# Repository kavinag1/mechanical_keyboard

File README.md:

# Building My Own 60% Mechanical Keyboard with a Raspberry Pi Pico

I have been wanting a mechanical keyboard. So instead of buying one why not make one. This was not really a easy journey but I am proud of what all I have learnt

---

## The Journey

### Step 0: Deciding the keyboard (1hr)
Over the past few days, I researched different types of keyboards to decide what I want to build. I compared layouts like 40%, 60%, 65%, and TKL, and chose a 60% layout because it offers a good balance between size and functionality while still being manageable to design. I also looked at existing open-source designs like the CO60 to understand how keyboard PCBs are structured and to confirm standard design practices.

I also researched switches, connectivity, and firmware. I selected EPOMAKER Creamy Jade switches because they are MX-style and compatible with standard footprints. I decided to make the keyboard wired instead of wireless to reduce complexity and allow me to use QMK firmware more easily.

The final specifications of my keyboard include a 60% layout, MX-style 5-pin switches, a row-column matrix with 1N4148 diodes, USB-C connectivity, and an STM32-based microcontroller. I will also include a rotary encoder for extra functionality and simple per-key backlighting. This research helped me clearly define my design before moving on to the PCB stage.

### Step 1: Learning What a Keyboard Matrix Is (1.5hr)

so before I could build this keyboard I needed to pratice what keyboard matrix is and understand how it works. So I followed a tutorial to make a simple and easy 3 by 3 keybaord matrix like the one you can see in the image. Keyboard matrix allows you to add more keys and use less number of pins like here I used 9 keys but only used 6 pins. This would be useful in the future when making the actual keyboard cause raspberry pico has only so many number of pins.

Once I understood the concept, I mapped out the full 60-key layout I wanted to build — a standard 60% ANSI arrangement: 5 rows and 14 columns.
this is the layout of the keyboard I went with

---

### Step 2: Designing the Schematic (2hr)

now after finalising the layout of my keyboard I needed to make the schematic of the keyboard. each key would need a switch and then a diode connected to it to prevnt phantom keypresses as if the diode are not present, when you are pressing multiple keys some keys you didnt press will also register and we dont want that. So I arranged the keys in a form of a matrix then conected the rows and collom pins to my GPIO pin in the pico. and then I also added a oled screen and a knob for the keyabord cause why not.

---

### Step 3: Routing the PCB (1hr)

With the schematic done, I moved on to laying out and routing the actual PCB. 

the peices I used are given in the BOM if you want to use the same parts

---

### Step 4:Writing the firmware (1.3hr)

The firmware was developed to act as the core software controlling the mechanical keyboard. I configured the keyboard's key matrix so that every physical switch was correctly mapped to its corresponding keycode and created a custom keymap defining the functionality of each key. 

### Step 5: adding the screen and the knob (3hr)

later on I wanted to add the knob and scren as well. for which I had to change the entire PCB again as I need to create more space for both of them. It took me some time to get the pcb right again. So I had to reroute all the wires makwe the scehmatic again and finally I was able to make it. I also had to make changes to the firmware code.

### Step 6: Designing the Case (2hr + 2hr)

I designed the case two times first was without the screen and the knob and was very basic because I spent time figuuring out how to add the spaces for the keyboard in the first design and then later I changed it to a more ergonomic design.

Then the final step was designing the case itself. For this I would reccomened exporting the PCB as a stl file and adding it in your cad to see if it fits your case or not. It saved me multiple times as I messed up the dimensions but this is the final case I eneded up with which perectly fits the PCB inside. for the case as you can see I went with a open desgin wherethe top part is open so that i can somewhat see the PCB just to remind me this is something I have created on my own.

### Step 7: making the case cooler (2hr)

after desiging the case I though of adding something on the back. For that I decided an engraving of the character brook from one peice./ So for that first i found and took inpiration from an arrt to create one fro the aspoect ratio of my keyboard. After which I uploaded the art on inkscape where i made the bitmap of the art. then i saved it as a dxf file which then I imported on onshape. AFter importing I resized itg and placed it on my case. I tried to extrude the whole sketch as it is but that didnt work because some part of the sketch broke. So I slowly divided it into difffernt parts and did it one by one. Overall I am pretty happy with the design.

## Bill of Materials

| Component | Purpose | Qty | Cost (USD) | Distributor | Link |
|-----------|---------|-----|-----------|-------------|------|
| Screen | The screen for the keyboard | 1 | $1.56 | Tech Delivers | [Buy](https://techdelivers.com/0-91-inch-oled-lcd-display-module-blue-128x32-i2c-iic-serial?tag=i2c%20lcd) |
| Micro USB Cable | To connect the Pico | 1 | $0.41 | robo craze | [Buy](https://robocraze.com/products/usb-to-micro-usb-cable?variant=40192442007705&country=IN&currency=INR&utm_medium=product_sync&utm_source=google&utm_content=sag_organic&utm_campaign=sag_organic&srsltid=AfmBOortLt6ed0G2jRT6m1UXHGk12v08zHm9dfpipg29VpxJJs0qQCNhlS8) |
| M2 Heat Set Inserts | For case assembly | 1 pack | $0.46 | Robu | [Buy]([https://www.amazon.in/BRASS-WAREHOUSE-Knurled-Threaded-Printing/dp/B0FMPZ3QHL/](https://robu.in/product/m2-x-4-mm-brass-insert/?gad_source=1&gad_campaignid=20387462343&gclid=CjwKCAjwqazPBhALEiwAOuXqdC2PIeLO9FYv27_n0XlEfAAc_tk7Q5QmU1Lylw90cpicqalJPc0k0xoC1_0QAvD_BwE&gbraid=0AAAAADvLFWezTS72c1S_AY11boPv9muTl)) |
| M2 Screws (20 pack) | Screwing the case | 1 pack | $1.5 | Robu | [Buy]([https://www.amazon.in/Tia-Golden-Screws-Length-Approx-480pcs/dp/B07VWKBHYZ/](https://robu.in/product/easymech-ss-304-csk-countersunk-philips-head-m2-x-8-mm-bolt-25-pcs/?gbraid=0AAAAADvLFWezTS72c1S_AY11boPv9muTl&gclid=CjwKCAjwqazPBhALEiwAOuXqdAjEcDjzmP8nFjrnLJZwyW1j_63GiNewVw8KRRNHgBSEja_1QjdDzRoC5vAQAvD_BwE&gad_source=1&gad_campaignid=20387462343) |
| Keycaps | Keycaps for the keyboard | 1 set | $13.5 | curisosity caps | [Buy]([https://meckeys.com/shop/accessories/keyboard-accessories/keycaps/grey-black-keycaps/](https://curiositycaps.in/products/cloud-lake-cherry-doubleshot-pbt-keycaps?_pos=14&_fid=805e1adb4&_ss=c)) |
| Gateron Switches | Switches for the keys | 7 packs | $13.37 | stackskb | [Buy]([https://meckeys.com/shop/accessories/keyboard-accessories/key-switches/gateron-optical-switch-pack/](https://stackskb.com/store/click-inc-of-linear-switch-pack-of-10/)) |
| Raspberry Pi Pico | The brain | 1 | $4.00 | Robu.in | [Buy](https://robu.in/product/raspberry-pi-pico/) |
| 3D Printed Case | The case | 1 | $16.18 | Robo In | — |
| DIODE | Its the diode for the circuit | 100 | $1.02 | Robu | [Buy]([https://www.amazon.in/Circuit-Ranger-Switching-Electronic-Projects/dp/B0FJLP12GX](https://robu.in/product/1n4148-1w-zener-diode-pack-of-50/?gclid=CjwKCAjwqazPBhALEiwAOuXqdDxSeVSHAfyNggbR2lhy_VAFvBNVaP29-qa4l7G2ySUgKkgBtbLfTRoC0zQQAvD_BwE&gad_campaignid=17427802703&gbraid=0AAAAADvLFWfPaMOUeeB-SFTwcKxeFjDbO&gad_source=1)) |
| PCB | It is the pcb of the keyboard | 5 | $64 | JLCPCB | — |
| **Total** | | | **$116** | | |

---

rols.

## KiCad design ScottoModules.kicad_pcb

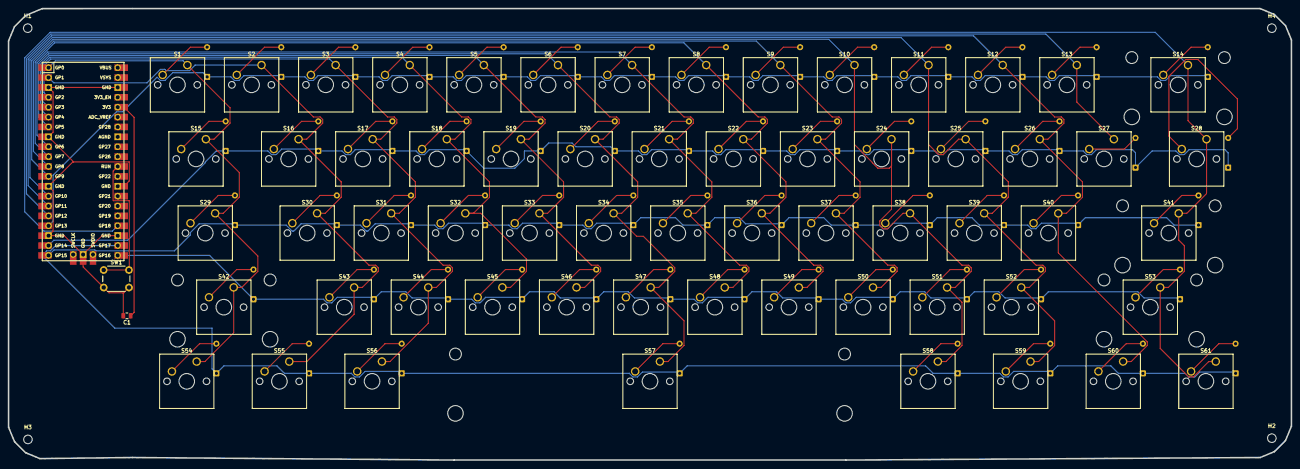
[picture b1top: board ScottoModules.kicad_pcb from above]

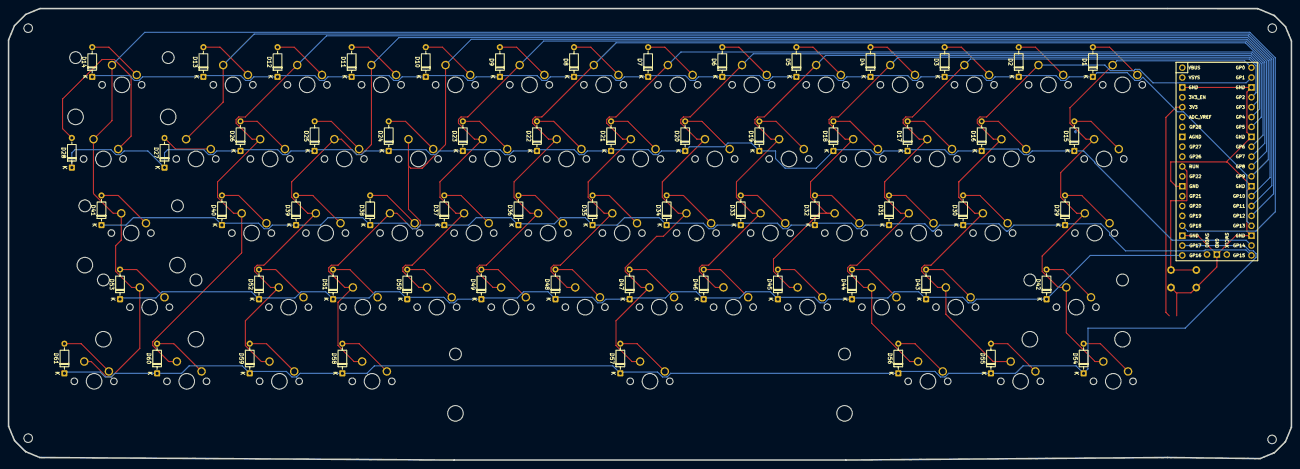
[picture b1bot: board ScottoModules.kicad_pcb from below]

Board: 4 copper layers, 329.7 x 116.0 mm, 129 parts (61 on the bottom side), 83 nets.

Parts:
C1: 0.1uF; C_0805_2012Metric
D1, D2, D3, D4, D5, D6, D7, D8, D9, D10, D11, D12, D13, D14, D15, D16, D17, D18, D19, D20, D21, D22, D23, D24, D25, D26, D27, D28, D29, D30, D31, D32, D33, D34, D35, D36, D37, D38, D39, D40, D41, D42, D43, D44, D45, D46, D47, D48, D49, D50, D51, D52, D53, D54, D55, D56, D57, D58, D59, D60, D61: D_DO-35_SOD27_P7.62mm_Horizontal
H1, H2, H3, H4: MountingHole; MountingHole_2.2mm_M2
S1, S2, S3, S4, S5, S6, S7, S8, S9, S10, S11, S12, S13, S16, S17, S18, S19, S20, S21, S22, S23, S24, S25, S26, S27, S30, S31, S32, S33, S34, S35, S36, S37, S38, S39, S40, S43, S44, S45, S46, S47, S48, S49, S50, S51, S52: SW_Cherry_MX_1.00u_PCB
S14: SW_Cherry_MX_2.00u_PCB
S15, S28: SW_Cherry_MX_1.50u_PCB
S29: SW_Cherry_MX_1.75u_PCB
S41, S42: SW_Cherry_MX_2.25u_PCB
S53: SW_Cherry_MX_2.75u_PCB
S54, S55, S56, S58, S59, S60, S61: SW_Cherry_MX_1.25u_PCB
S57: SW_Cherry_MX_6.25u_PCB
SW1: SW_Push; SW_PUSH_6mm
U2: Raspberry_Pi_Pico

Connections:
GND: C1.2, SW1.2, U2.3 (GND), U2.8 (GND), U2.13 (GND), U2.18 (GND), U2.23 (GND), U2.28 (GND), U2.38 (GND), U2.42 (GND)
unnamed: D1.2 (A), S1.2
unnamed: D2.2 (A), S2.2
unnamed: D3.2 (A), S3.2
unnamed: D4.2 (A), S4.2
unnamed: D5.2 (A), S5.2
unnamed: D6.2 (A), S6.2
unnamed: D7.2 (A), S7.2
unnamed: D8.2 (A), S8.2
unnamed: D9.2 (A), S9.2
unnamed: D10.2 (A), S10.2
unnamed: D11.2 (A), S11.2
unnamed: D12.2 (A), S12.2
unnamed: D13.2 (A), S13.2
unnamed: D14.2 (A), S14.2
unnamed: D15.2 (A), S15.2
unnamed: D16.2 (A), S16.2
unnamed: D17.2 (A), S17.2
unnamed: D18.2 (A), S18.2
unnamed: D19.2 (A), S19.2
unnamed: D20.2 (A), S20.2
unnamed: D21.2 (A), S21.2
unnamed: D22.2 (A), S22.2
unnamed: D23.2 (A), S23.2
unnamed: D24.2 (A), S24.2
unnamed: D25.2 (A), S25.2
unnamed: D26.2 (A), S26.2
unnamed: D27.2 (A), S27.2
unnamed: D28.2 (A), S28.2
unnamed: D29.2 (A), S29.2
unnamed: D30.2 (A), S30.2
unnamed: D31.2 (A), S31.2
unnamed: D32.2 (A), S32.2
unnamed: D33.2 (A), S33.2
unnamed: D34.2 (A), S34.2
unnamed: D35.2 (A), S35.2
unnamed: D36.2 (A), S36.2
unnamed: D37.2 (A), S37.2
unnamed: D38.2 (A), S38.2
unnamed: D39.2 (A), S39.2
unnamed: D40.2 (A), S40.2
unnamed: D41.2 (A), S41.2
unnamed: D42.2 (A), S42.2
unnamed: D43.2 (A), S43.2
unnamed: D44.2 (A), S44.2
unnamed: D45.2 (A), S45.2
unnamed: D46.2 (A), S46.2
unnamed: D47.2 (A), S47.2
unnamed: D48.2 (A), S48.2
unnamed: D49.2 (A), S49.2
unnamed: D50.2 (A), S50.2
unnamed: D51.2 (A), S51.2
unnamed: D52.2 (A), S52.2
unnamed: D53.2 (A), S53.2
unnamed: D54.2 (A), S54.2
unnamed: D55.2 (A), S55.2
unnamed: D56.2 (A), S56.2
unnamed: D57.2 (A), S57.2
unnamed: D58.2 (A), S58.2
unnamed: D59.2 (A), S59.2
unnamed: D60.2 (A), S60.2
unnamed: D61.2 (A), S61.2
unnamed: C1.1, U2.36 (3V3)
column 0: S1.1, S15.1, S29.1, S42.1, S54.1, U2.1 (GPIO0)
column 1: S2.1, S16.1, S30.1, S43.1, S55.1, U2.2 (GPIO1)
column 2: S3.1, S17.1, S31.1, S44.1, S56.1, U2.4 (GPIO2)
column 3: S4.1, S18.1, S32.1, S45.1, U2.5 (GPIO3)
column 4: S5.1, S19.1, S33.1, S46.1, U2.6 (GPIO4)
column 5: S6.1, S20.1, S34.1, S47.1, S57.1, U2.7 (GPIO5)
column 6: S7.1, S21.1, S35.1, S48.1, U2.9 (GPIO6)
column 7: S8.1, S22.1, S36.1, S49.1, U2.10 (GPIO7)
column 8: S9.1, S23.1, S37.1, S50.1, U2.11 (GPIO8)
column 9: S10.1, S24.1, S38.1, S51.1, S58.1, U2.12 (GPIO9)
column 10: S11.1, S25.1, S39.1, S52.1, S59.1, U2.14 (GPIO10)
column 11: S12.1, S26.1, S40.1, S60.1, U2.15 (GPIO11)
column 12: S13.1, S27.1, U2.16 (GPIO12)
column 13: S14.1, S28.1, S41.1, S53.1, S61.1, U2.24 (GPIO18)
row 0: D1.1 (K), D2.1 (K), D3.1 (K), D4.1 (K), D5.1 (K), D6.1 (K), D7.1 (K), D8.1 (K), D9.1 (K), D10.1 (K), D11.1 (K), D12.1 (K), D13.1 (K), D14.1 (K), U2.17 (GPIO13)
row 1: D15.1 (K), D16.1 (K), D17.1 (K), D18.1 (K), D19.1 (K), D20.1 (K), D21.1 (K), D22.1 (K), D23.1 (K), D24.1 (K), D25.1 (K), D26.1 (K), D27.1 (K), D28.1 (K), U2.19 (GPIO14)
row 2: D29.1 (K), D30.1 (K), D31.1 (K), D32.1 (K), D33.1 (K), D34.1 (K), D35.1 (K), D36.1 (K), D37.1 (K), D38.1 (K), D39.1 (K), D40.1 (K), D41.1 (K), U2.20 (GPIO15)
row 3: D42.1 (K), D43.1 (K), D44.1 (K), D45.1 (K), D46.1 (K), D47.1 (K), D48.1 (K), D49.1 (K), D50.1 (K), D51.1 (K), D52.1 (K), D53.1 (K), U2.21 (GPIO16)
row 4: D54.1 (K), D55.1 (K), D56.1 (K), D57.1 (K), D58.1 (K), D59.1 (K), D60.1 (K), D61.1 (K), U2.22 (GPIO17)
run: SW1.1, U2.30 (RUN)

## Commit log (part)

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2026-04-04 Initial commit: 60% mechanical keyboard firmware for Raspberry Pi Pico
2026-04-04 Convert to QMK firmware with actual PCB pinout configuration
    - Update GPIO pin assignments to match PCB layout (GP13-17 rows, GP0-12+GP18 columns)
    - Create QMK config.h with correct matrix size and pin definitions
    - Add keymaps/default/keymap.c with QWERTY layer and function layer
    - Create rules.mk and info.json for QMK build system
    - Add comprehensive QMK documentation for GPIO pinout and customization
    - Include INSTALL.md with QMK compilation and flashing instructions
2026-04-04 Create comprehensive build guide README
    - Complete step-by-step assembly instructions
    - Detailed component list and cost breakdown
    - Hardware assembly phases (firmware, PCB, switches)
    - Comprehensive troubleshooting section
    - Customization guide with examples
    - References to design process and documentation
2026-04-04 Add GitHub setup instructions for publishing project
2026-04-04 Fix: Remove duplicate DEBOUNCE definition in config.h
2026-04-04 Fix: Remove duplicate BOOTLOADER definition in rules.mk
2026-04-04 Add project completion checklist and verification document
2026-04-04 Simplify project: remove unnecessary files, streamline code and docs
2026-04-04 Clean up keymap.c - remove leftover comment code
2026-04-04 Final cleanup: remove all optional comments from config.h and rules.mk
2026-04-04 Remove split keyboard optional comments from config.h
2026-04-04 Further simplify README - only steps taken, remove all reference material
2026-04-04 Make README more human and narrative - tell the actual build story
2026-04-04 Add human narrative README and image placeholders for build documentation
2026-04-04 Add ASCII diagrams, circuit explanation, and troubleshooting guide to README
2026-04-04 Add GitHub upload instructions for easy publishing
2026-04-04 Format: add newline at end of files
2026-04-04 Add automated GitHub upload PowerShell script
2026-04-04 Update upload guide to mention automated script
2026-04-04 Add quick start guide for GitHub upload
2026-04-05 improve README: add all 11 real screenshots, more personal journey narrative
    Agent-Logs-Url: https://github.com/kavinag1/mechanical_keyboard/sessions/986a66d9-50ec-4b9c-9d99-0dcddae88fbd
2026-04-05 Add BOM table to README.md
    Agent-Logs-Url: https://github.com/kavinag1/mechanical_keyboard/sessions/757ec243-e3ee-478e-9da1-cacf7cee7caa
2026-04-05 Delete unnecessary GitHub upload helper files
    Agent-Logs-Url: https://github.com/kavinag1/mechanical_keyboard/sessions/cc6ed61a-44dc-4852-bda4-a392d2791f0e
2026-04-05 Reorganize files into folders: cad/, pcb/, production_material/, firmware/
    - Rename 'Part Studio 2.step' to cad/bottom_case.step
    - Rename 'Part Studio 3.step' to cad/top_case.step
    - Move KiCad PCB files to pcb/
    - Move BOM and gerbers to production_material/
    - Move firmware files (config.h, rules.mk, info.json, keymaps/) to firmware/
    - Update README with new repository structure section
2026-04-05 Rewrite README: reorder steps, add 3x3 matrix intro, remove soldering/assembly/testing/file structure/troubleshooting sections
    Agent-Logs-Url: https://github.com/kavinag1/mechanical_keyboard/sessions/55de234f-2cd9-4d56-9ed2-190bfe4a9fce
2026-04-05 Reorganize and label images; update README to use descriptive filenames
    Agent-Logs-Url: https://github.com/kavinag1/mechanical_keyboard/sessions/fd048f3d-3194-4360-889d-65fd1ae51220
2026-04-12 feat: add OLED display and rotary encoder support
    - config.h: add I2C1 pins for OLED (SCL=GP26, SDA=GP25) and encoder pins (A=GP27, B=GP29)
    - rules.mk: enable OLED_ENABLE, ENCODER_ENABLE, ENCODER_MAP_ENABLE
    - keymap.c: add oled_task_user() for layer/mod/lock display, add encoder_map for vol/media
    - docs/pinout.md: document OLED and encoder pins and configuration
    - README.md: add OLED and encoder to pin assignments and BOM
    Agent-Logs-Url: https://github.com/kavinag1/mechanical_keyboard/sessions/acb1897e-aee5-4937-a9d0-ccdec6fea8e2
2026-04-12 fix: use I2CD2 for I2C driver name and fix OLED spacing
    Agent-Logs-Url: https://github.com/kavinag1/mechanical_keyboard/sessions/acb1897e-aee5-4937-a9d0-ccdec6fea8e2
2026-04-12 Update keyboard build images and BOM
2026-04-12 Update README, CAD model, and image set
2026-04-24 Update BOM with new prices, quantities, and distributors
    Agent-Logs-Url: https://github.com/kavinag1/mechanical_keyboard/sessions/7156329a-06fe-4bd5-bbe3-e064ff1e64a8
2026-04-25 remove BOM items 3 and 4 (reset button and capacitor), update README total
    Agent-Logs-Url: https://github.com/kavinag1/mechanical_keyboard/sessions/9bd4889d-3662-482a-bfb3-7f0437decefc
2026-05-10 Revise README for clarity and personal insights
    Revised the introduction and journey sections for clarity and personal experience. Updated the explanation of the keyboard matrix and its layout.
2026-06-29 Add BOM.csv with bill of materials
